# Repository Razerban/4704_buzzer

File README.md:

# 4704_buzzer
A recreation of the IBM 4704 Series buzzer board

This board has been reverse engineered from a buzzer board found in a genuine IBM 4704 Series Model F 107 keyboard.

# PCB design notes
Due to the physical constraints of the space available inside the IBM 4704 Series Model F keyboard cases for housing the buzzer board, only 7.5mm of height is available to house a physical buzzer mounted on the top of the PCB.
However, due to the availability and different shapes and dimensions (and the cost) of the buzzers available in the market, it's not easy (and cheap) to find one that would satisfy these constraints.
So I decided to add a second footprint on the bottom of the PCB that would allow to take advantage of the space available underneath the board to house a bigger buzzer.

The maximum dimensions of the buzzers that would be compatible with this board are:
- BZ1 (Buzzer installed on the bottom of the PCB): L=30mm, W=30mm, H=16.5mm

- BZ2 (Buzzer installed on the top of the PCB): L=22mm, W=22mm, H=7mm

These dimensions work for 1.6mm thick PCB boards.
While I don't recommend this, you could choose a less thick PCB when ordering the board from your PCB Fabrication Manufacturer.
This would let you choose a bigger (height wise) buzzer to mount on the top or bottom of the PCB, however, beware that the PCB might not be able to sit correctly inside the case.

# Ordering from JLCPCB
1) Go to http://jlcpcb.com , sign in to your account (create one if you don't have one)
2) Click Order Now
3) Upload the .zip file from the "production" subfolder
4) Select PCB Qty you wish to build
5) Set "Remove Order Number" to "Specify a location"

# BOM
- C1: 20nF
- C2: 20nF
- C3: 7nF
- R1: 330
- R2: 27K
- R3: 27K
- RV1: 20K (I recommend Bourns 3345P-1-203-T)

# License
You can redistribute this project and/or modify it under the terms of the
GNU General Public License as published by the Free Software Foundation,
either version 3 of the License, or (at your option) any later version.

This program is distributed in the hope that it will be useful,
but WITHOUT ANY WARRANTY; without even the implied warranty of
MERCHANTABILITY or FITNESS FOR A PARTICULAR PURPOSE.  See the
GNU General Public License for more details.

You should have received a copy of the GNU General Public License
along with this program.  If not, see <http://www.gnu.org/licenses/>.

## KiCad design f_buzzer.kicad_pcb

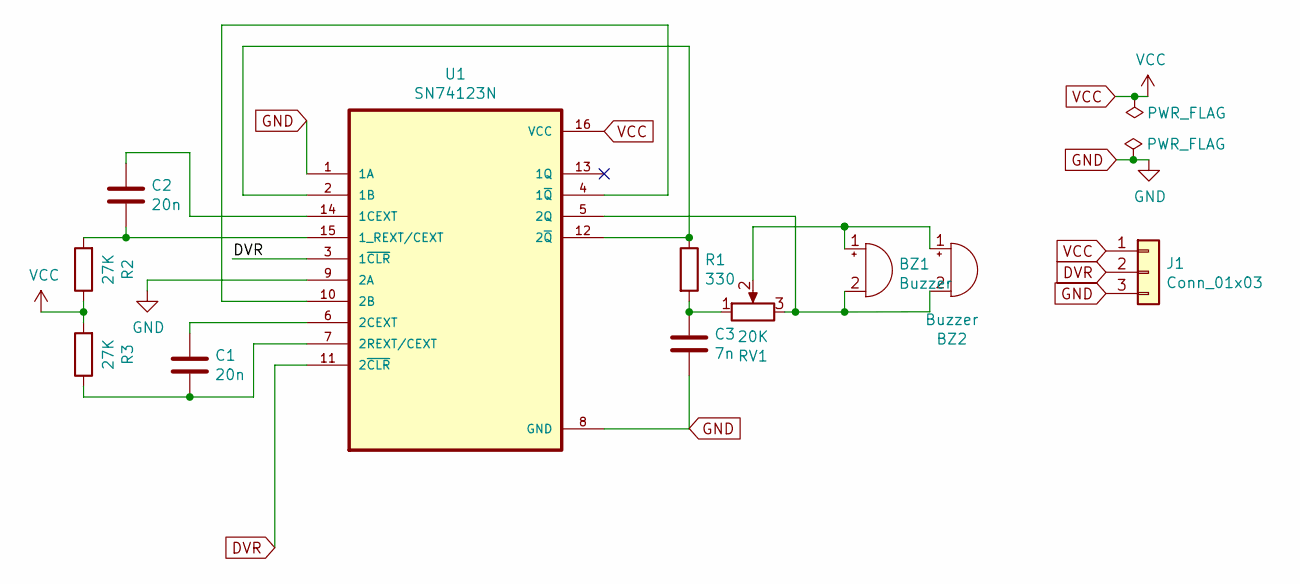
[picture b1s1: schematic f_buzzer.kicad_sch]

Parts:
BZ1: Buzzer; buzzer_bottom
BZ2: Buzzer; buzzer_front
C1, C2: 20n; C_Disc_D5.1mm_W3.2mm_P5.00mm
C3: 7n; C_Disc_D5.1mm_W3.2mm_P5.00mm
J1: Conn_01x03; PinHeader_1x03_P2.54mm_Horizontal
R1: 330; R_Axial_DIN0207_L6.3mm_D2.5mm_P7.62mm_Horizontal
R2, R3: 27K; R_Axial_DIN0207_L6.3mm_D2.5mm_P7.62mm_Horizontal
RV1: 20K; Potentiometer_Bourns_3345P_Horizontal
U1: SN74123N; DIP-16_W7.62mm_Socket

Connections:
DVR: J1.2, U1.3 (1~CLR), U1.11 (2~CLR)
GND: C3.2, J1.3, U1.1 (1A), U1.8 (GND), U1.9 (2A)
unnamed: BZ1.1 (-), BZ2.1 (-), RV1.2
unnamed: BZ1.2 (+), BZ2.2 (+), RV1.3, U1.5 (2Q)
unnamed: C1.1, U1.6 (2CEXT)
unnamed: C1.2, R3.1, U1.7 (2REXT/CEXT)
unnamed: C2.1, U1.14 (1CEXT)
unnamed: C2.2, R2.2, U1.15 (1_REXT/CEXT)
unnamed: C3.1, R1.2, RV1.1
unnamed: R1.1, U1.2 (1B), U1.12 (2~Q)
unnamed: U1.4 (1~Q), U1.10 (2B)
VCC: J1.1, R2.1, R3.2, U1.16 (VCC)

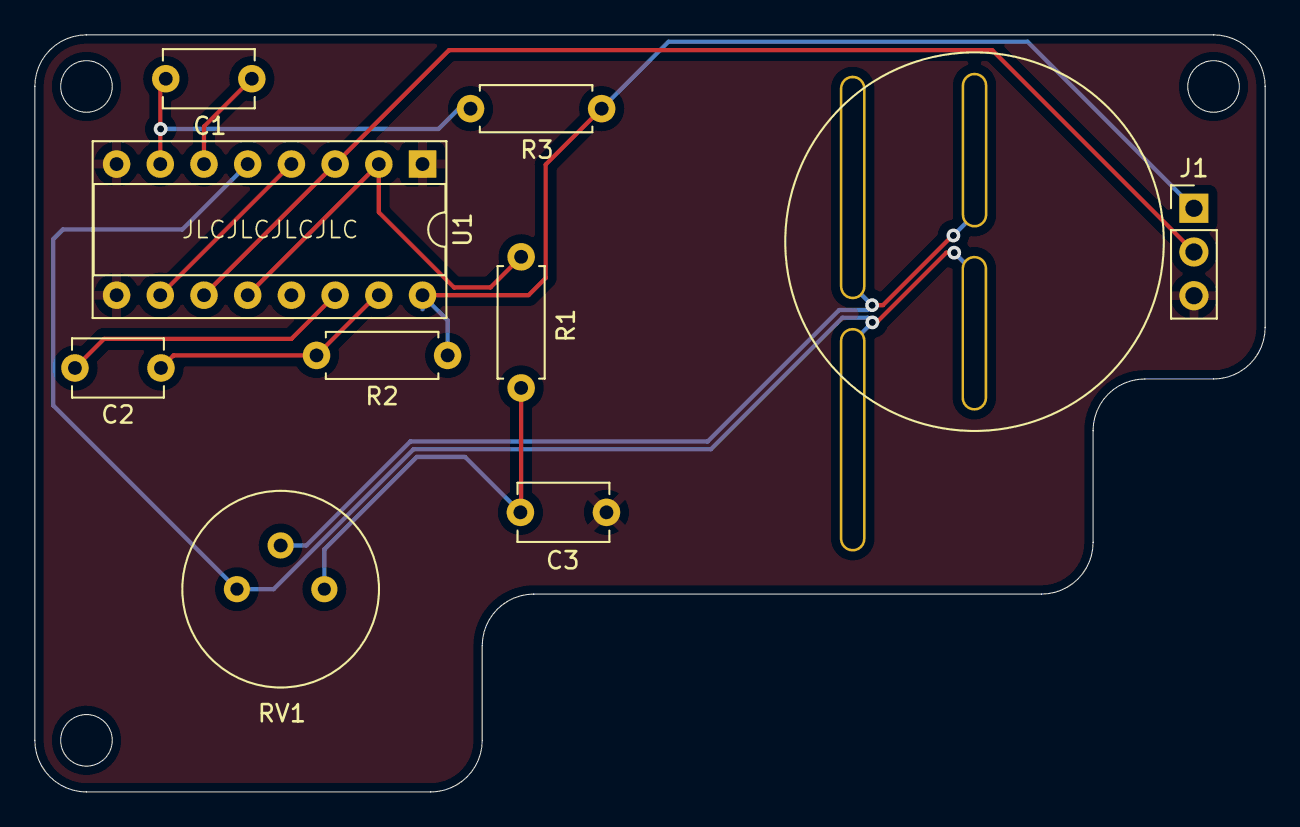
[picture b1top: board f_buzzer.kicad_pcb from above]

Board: 2 copper layers, 71.5 x 44.0 mm, 11 parts (1 on the bottom side), 12 nets.

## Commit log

2021-02-05 Added .gitignore
2021-02-05 Initial sketch
2021-02-06 Added the 3D model for the potentiometer
2021-02-06 Added library for the SN74123N chip
2021-02-06 Rev1
2021-02-06 Fixed connections in schematic
2021-02-06 Added some constraints related to the case
2021-02-06 Created a generic footprint for 22mm (diameter) Buzzer
2021-02-06 Created a generic footprint for 28mm (diameter) Buzzer
2021-02-06 Replaced the buzzer with the 22mm generic one
2021-02-06 Changed the footprint to be able to house 30mm (diameter) buzzers
2021-02-06 Added 3D models for the footprints
2021-02-06 Placed the two buzzers for 3D rendering of the board
2021-02-06 Added fill zones
2021-02-06 Relocated some components
2021-02-06 Added JLCPCB magic string
2021-02-06 Added notes about the maximum dimensions of the buzzers
2021-02-09 Colored the 3D models
2021-02-09 Added C3 value to the schematic
2021-02-09 Updated README file and added GNU GPL3 as the project's license
2021-02-09 Updated latest gerbers file
2021-02-13 First SMD revision
2021-02-13 Added datasheets
2021-02-13 Changed the buzzer footprints
2021-02-13 Updated the buzzer footprints
2021-02-13 Updated the SN74LS123DRG4 footprint
2021-02-13 Added JLCPCB SMT production files
2021-02-13 Added VG039NCHXTB203 Potentiometer footprint
2021-02-13 Updated the schematics and pcb design
2021-02-28 Changed the potentiometer footprint
2022-01-16 Update to KiCad 6
2022-01-17 Update the footprints to SMD ones
2022-01-17 Rearranged the components
2022-01-17 Added latest gerber version
